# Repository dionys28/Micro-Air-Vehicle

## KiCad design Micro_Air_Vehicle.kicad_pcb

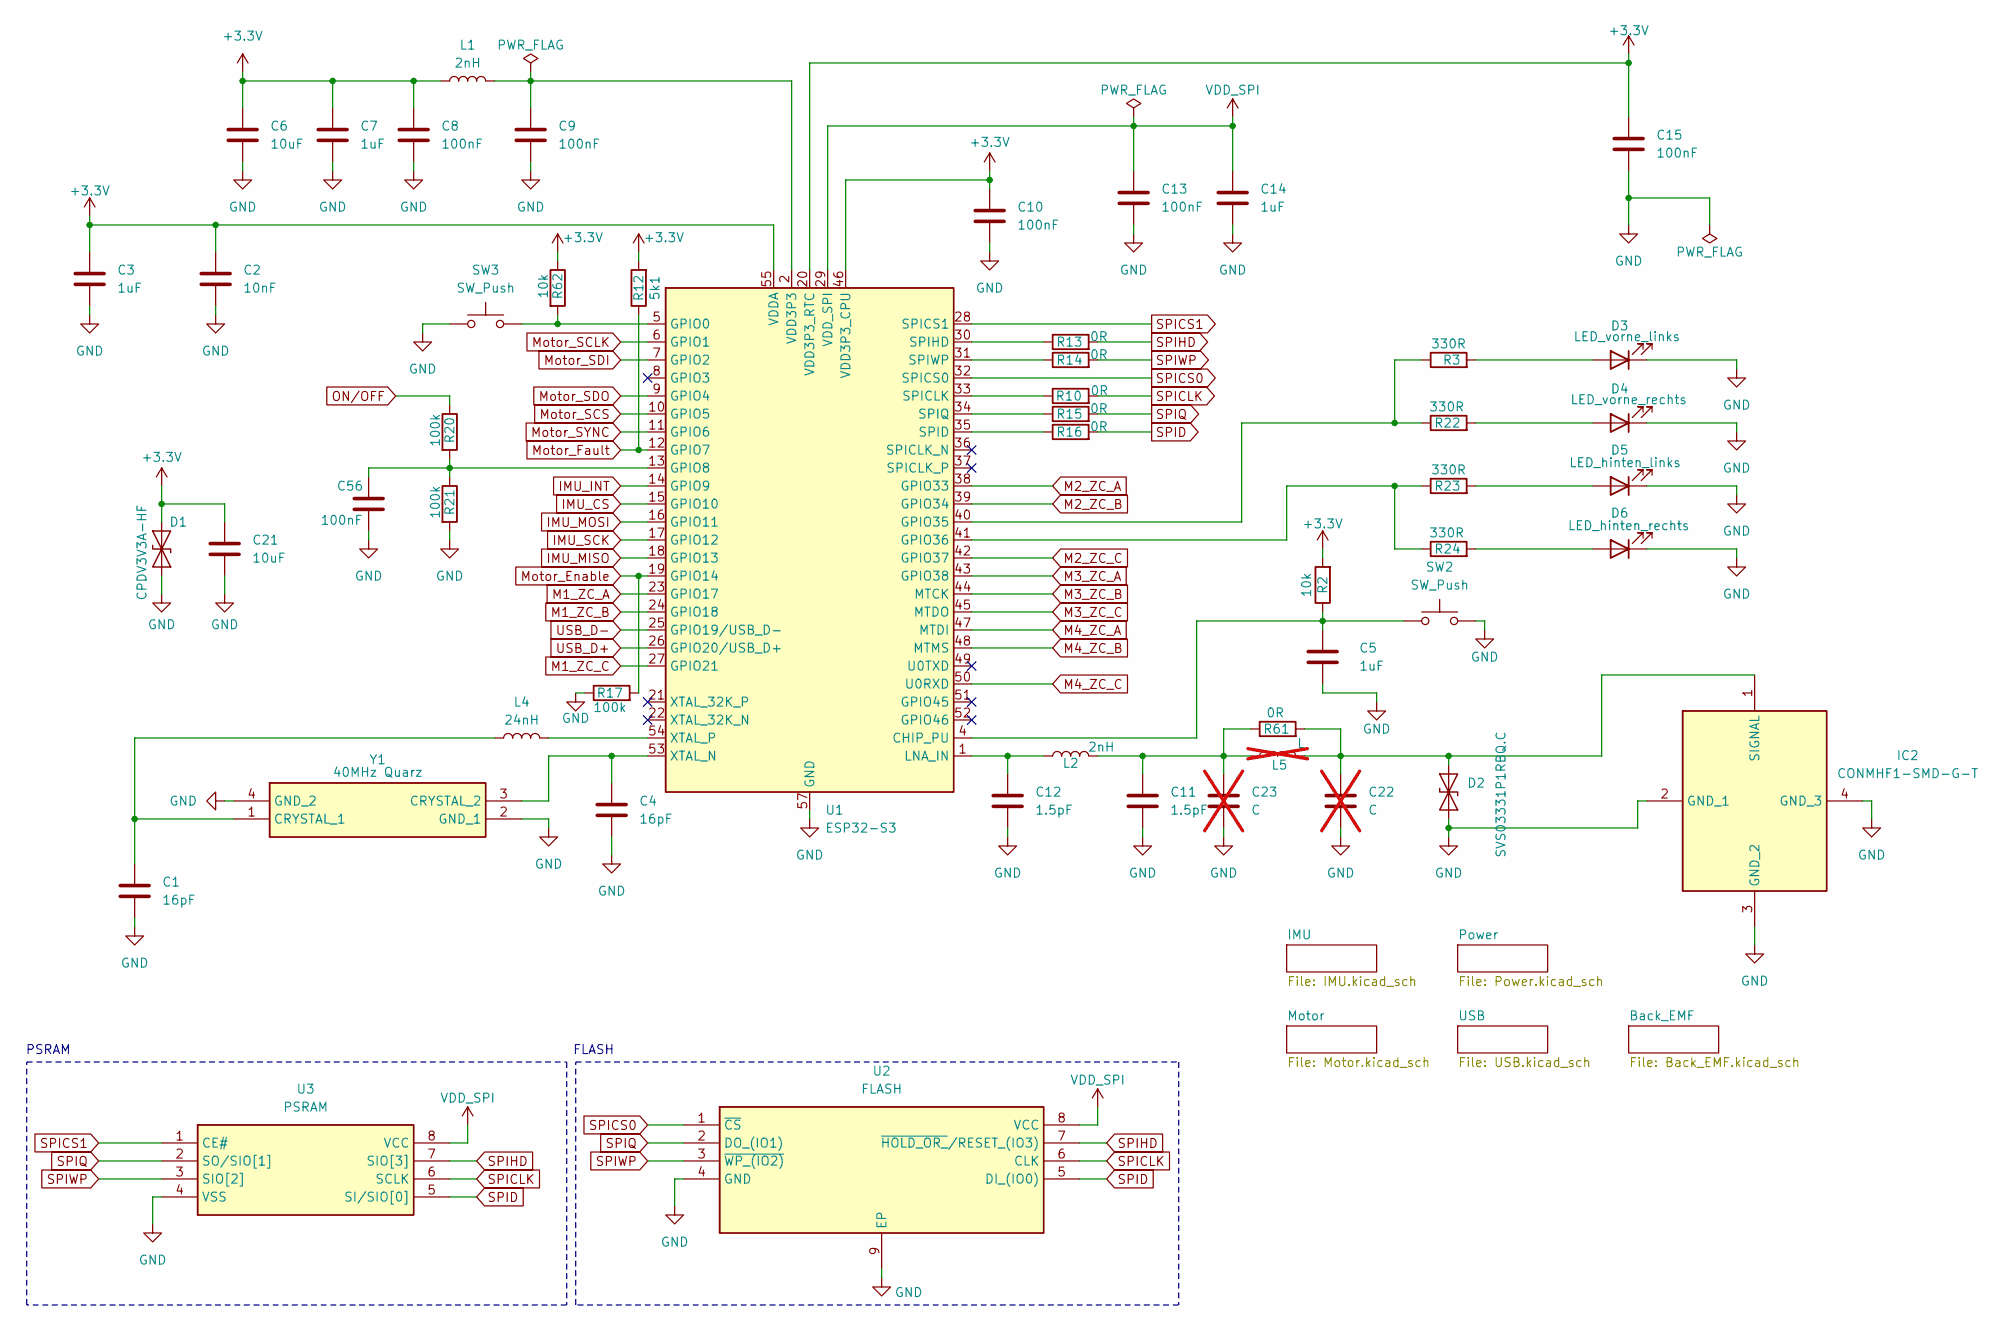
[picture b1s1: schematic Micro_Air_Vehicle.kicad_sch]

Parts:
C1, C4: 16pF; C_0603_1608Metric; LCSC Part # C1646
C2: 10nF; C_0603_1608Metric; LCSC Part # C1589
C3, C5, C7, C14: 1uF; C_0805_2012Metric; LCSC Part # C1712
C6, C21: 10uF; C_0805_2012Metric; LCSC Part # C15850
C8, C9, C10, C13, C15, C56: 100nF; C_0603_1608Metric; LCSC Part # C1590
C11, C12: 1.5pF; C_0201_0603Metric; LCSC Part # C50389
C22, C23: C; C_0201_0603Metric; not fitted
D1: CPDV3V3A-HF; Diode_D1; LCSC Part # C2594895
D2: SVS03331P1RBQ.C; LCSC Part # C19829538
D3: LED_vorne_links; LED_1206_3216Metric; LCSC Part # C219232
D4: LED_vorne_rechts; LED_1206_3216Metric; LCSC Part # C219232
D5: LED_hinten_links; LED_1206_3216Metric; LCSC Part # C49018
D6: LED_hinten_rechts; LED_1206_3216Metric; LCSC Part # C49018
IC2: CONMHF1-SMD-G-T; Antennen_Stecker; Mouser Part Number 712-CONMHF1-SMD-G-T
L1, L2: 2nH; L_0201_0603Metric; LCSC Part # C42142
L4: 24nH; L_0201_0603Metric; LCSC Part # C206441
L5: L; L_0201_0603Metric; not fitted
R2, R62: 10k; R_0603_1608Metric; LCSC Part # C15401
R3, R22, R23, R24: 330R; R_0603_1608Metric; LCSC Part # C22104
R10, R13, R14, R15, R16, R61: 0R; R_0603_1608Metric; LCSC Part # C21189
R12: 5k1; R_0603_1608Metric; LCSC Part # C14677
R17, R20, R21: 100k; R_0603_1608Metric; LCSC Part # C14675
SW2, SW3: SW_Push; SW_Push_1P1T_NO_CK_KMR2; LCSC Part # C99271
U1: ESP32-S3; QFN-56-1EP_7x7mm_P0.4mm_EP4x4mm; LCSC Part # C2913192
U2: FLASH; Mouser Part Number 454-W25Q64JVZPIM
U3: PSRAM; Mouser Part Number 485-4677
Y1: 40MHz Quarz; 40MHz_Quarz; Mouser Part Number 710-830108208709

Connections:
+3.3V: C2.1, C3.1, C6.1, C7.1, C8.1, C10.1, C15.1, C21.1, D1.2 (A2), L1.1, R2.2, R12.2, R62.1, U1.20 (VDD3P3_RTC), U1.46 (VDD3P3_CPU), U1.55 (VDDA), U1.56 (VDDA); also elsewhere on the board
GND: C1.2, C2.2, C3.2, C4.2, C5.2, C6.2, C7.2, C8.2, C9.2, C10.2, C11.2, C12.2, C13.2, C14.2, C15.2, C21.2, C22.2, C23.2, C56.2, D1.1 (A1), D2.1 (A1), D3.1 (K), D4.1 (K), D5.1 (K), D6.1 (K), IC2.2 (GND_1), IC2.3 (GND_2), IC2.4 (GND_3), R17.1, R21.2, SW2.2, SW3.1, U1.57 (GND), U2.4 (GND), U2.9 (EP), U3.4 (VSS), Y1.2 (GND_1), Y1.4 (GND_2); also elsewhere on the board
IMU_CS: U1.15 (GPIO10); also elsewhere on the board
IMU_INT: U1.14 (GPIO9); also elsewhere on the board
IMU_MISO: U1.18 (GPIO13); also elsewhere on the board
IMU_MOSI: U1.16 (GPIO11); also elsewhere on the board
IMU_SCK: U1.17 (GPIO12); also elsewhere on the board
M1_ZC_A: U1.23 (GPIO17); also elsewhere on the board
M1_ZC_B: U1.24 (GPIO18); also elsewhere on the board
M1_ZC_C: U1.27 (GPIO21); also elsewhere on the board
M2_ZC_A: U1.38 (GPIO33); also elsewhere on the board
M2_ZC_B: U1.39 (GPIO34); also elsewhere on the board
M2_ZC_C: U1.42 (GPIO37); also elsewhere on the board
M3_ZC_A: U1.43 (GPIO38); also elsewhere on the board
M3_ZC_B: U1.44 (MTCK); also elsewhere on the board
M3_ZC_C: U1.45 (MTDO); also elsewhere on the board
M4_ZC_A: U1.47 (MTDI); also elsewhere on the board
M4_ZC_B: U1.48 (MTMS); also elsewhere on the board
M4_ZC_C: U1.50 (U0RXD); also elsewhere on the board
Motor_Enable: R17.2, U1.19 (GPIO14); also elsewhere on the board
Motor_Fault: R12.1, U1.12 (GPIO7); also elsewhere on the board
Motor_SCLK: U1.6 (GPIO1); also elsewhere on the board
Motor_SCS: U1.10 (GPIO5); also elsewhere on the board
Motor_SDI: U1.7 (GPIO2); also elsewhere on the board
Motor_SDO: U1.9 (GPIO4); also elsewhere on the board
Motor_SYNC: U1.11 (GPIO6); also elsewhere on the board
unnamed: C9.1, L1.2, U1.2 (VDD3P3), U1.3 (VDD3P3)
unnamed: C11.1, C23.1, L2.2, L5.1, R61.1
unnamed: C22.1, D2.2 (A2), IC2.1 (SIGNAL), L5.2, R61.2
unnamed: D3.2 (A), R3.2
unnamed: D4.2 (A), R22.2
unnamed: D5.2 (A), R23.2
unnamed: D6.2 (A), R24.2
unnamed: C5.1, R2.1, SW2.1, U1.4 (CHIP_PU)
unnamed: R62.2, SW3.2, U1.5 (GPIO0)
unnamed: C56.1, R20.2, R21.1, U1.13 (GPIO8)
unnamed: R3.1, R22.1, U1.40 (GPIO35)
unnamed: R23.1, R24.1, U1.41 (GPIO36)
unnamed: C12.1, L2.1, U1.1 (LNA_IN)
unnamed: R10.1, U1.33 (SPICLK)
unnamed: R16.1, U1.35 (SPID)
unnamed: R13.1, U1.30 (SPIHD)
unnamed: R15.1, U1.34 (SPIQ)
unnamed: R14.1, U1.31 (SPIWP)
unnamed: C4.1, U1.53 (XTAL_N), Y1.3 (CRYSTAL_2)
unnamed: L4.2, U1.54 (XTAL_P)
unnamed: C1.1, L4.1, Y1.1 (CRYSTAL_1)
ON/OFF: R20.1; also elsewhere on the board
SPICLK: R10.2, U2.6 (CLK), U3.6 (SCLK)
SPICS0: U1.32 (SPICS0), U2.1 (~CS)
SPICS1: U1.28 (SPICS1), U3.1 (CE#)
SPID: R16.2, U2.5 (DI_(IO0)), U3.5 (SI/SIO[0])
SPIHD: R13.2, U2.7 (~HOLD_OR_/RESET_(IO3)), U3.7 (SIO[3])
SPIQ: R15.2, U2.2 (DO_(IO1)), U3.2 (SO/SIO[1])
SPIWP: R14.2, U2.3 (~WP_(IO2)), U3.3 (SIO[2])
USB_D+: U1.26 (GPIO20/USB_D+); also elsewhere on the board
USB_D-: U1.25 (GPIO19/USB_D-); also elsewhere on the board
VDD_SPI: C13.1, C14.1, U1.29 (VDD_SPI), U2.8 (VCC), U3.8 (VCC)

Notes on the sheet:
PSRAM
FLASH

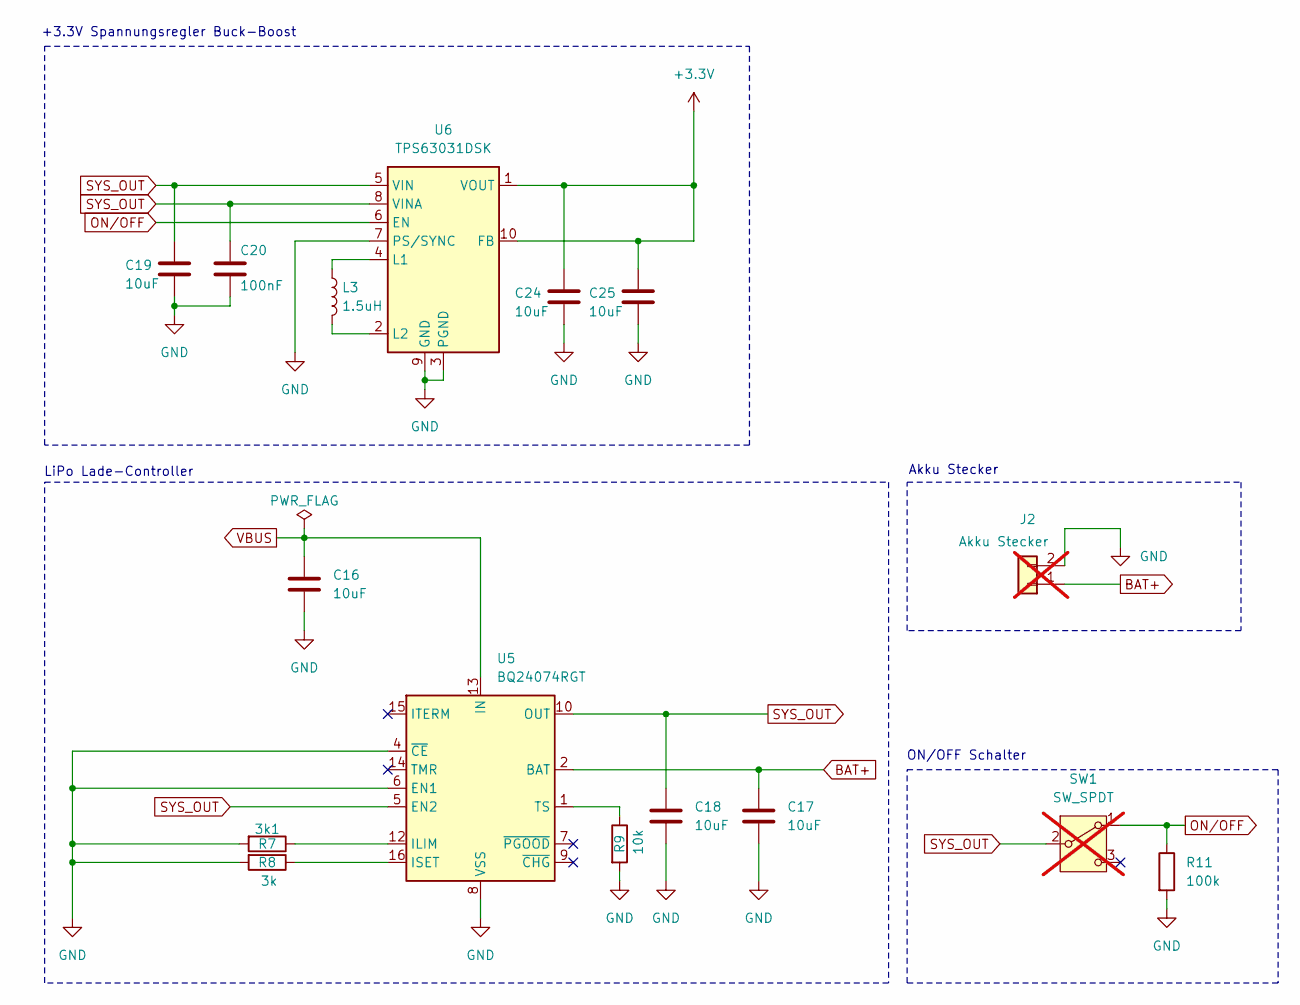
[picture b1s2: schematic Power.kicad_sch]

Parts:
C16, C17, C18, C19, C24, C25: 10uF; C_0805_2012Metric; LCSC Part # C15850
C20: 100nF; C_0603_1608Metric; LCSC Part # C1590
J2: Akku Stecker; SolderWire-1sqmm_1x02_P5.4mm_D1.4mm_OD2.7mm; not fitted
L3: 1.5uH; Spule1.5uH; LCSC Part # C2762016
R7: 3k1; R_0603_1608Metric; LCSC Part # C2924132
R8: 3k; R_0603_1608Metric; LCSC Part # C4211
R9: 10k; R_0603_1608Metric; LCSC Part # C15401
R11: 100k; R_0603_1608Metric; LCSC Part # C14675
SW1: SW_SPDT; SW_SPDT_CK_JS102011SAQN; not fitted
U5: BQ24074RGT; VQFN-16-1EP_3x3mm_P0.5mm_EP1.68x1.68mm_ThermalVias; LCSC Part # C54313
U6: TPS63031DSK; WSON-10-1EP_2.5x2.5mm_P0.5mm_EP1.2x2mm_ThermalVias; LCSC Part # C15516

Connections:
+3.3V: C24.1, C25.1, U6.1 (VOUT), U6.10 (FB); also elsewhere on the board
BAT+: C17.1, J2.1, U5.2 (BAT), U5.3 (BAT); also elsewhere on the board
GND: C16.2, C17.2, C18.2, C19.2, C20.2, C24.2, C25.2, J2.2, R7.2, R8.2, R9.2, R11.2, U5.4 (~CE), U5.6 (EN1), U5.8 (VSS), U5.17 (VSS), U6.3 (PGND), U6.7 (PS/SYNC), U6.9 (GND), U6.11 (PGND); also elsewhere on the board
unnamed: R7.1, U5.12 (ILIM)
unnamed: R8.1, U5.16 (ISET)
unnamed: R9.1, U5.1 (TS)
unnamed: L3.1, U6.4 (L1)
unnamed: L3.2, U6.2 (L2)
ON/OFF: R11.1, SW1.1 (A), U6.6 (EN); also elsewhere on the board
SYS_OUT: C18.1, C19.1, C20.1, SW1.2 (B), U5.5 (EN2), U5.10 (OUT), U5.11 (OUT), U6.5 (VIN), U6.8 (VINA); also elsewhere on the board
VBUS: C16.1, U5.13 (IN); also elsewhere on the board

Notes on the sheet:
ON/OFF Schalter
Akku Stecker
+3.3V Spannungsregler Buck-Boost
LiPo Lade-Controller

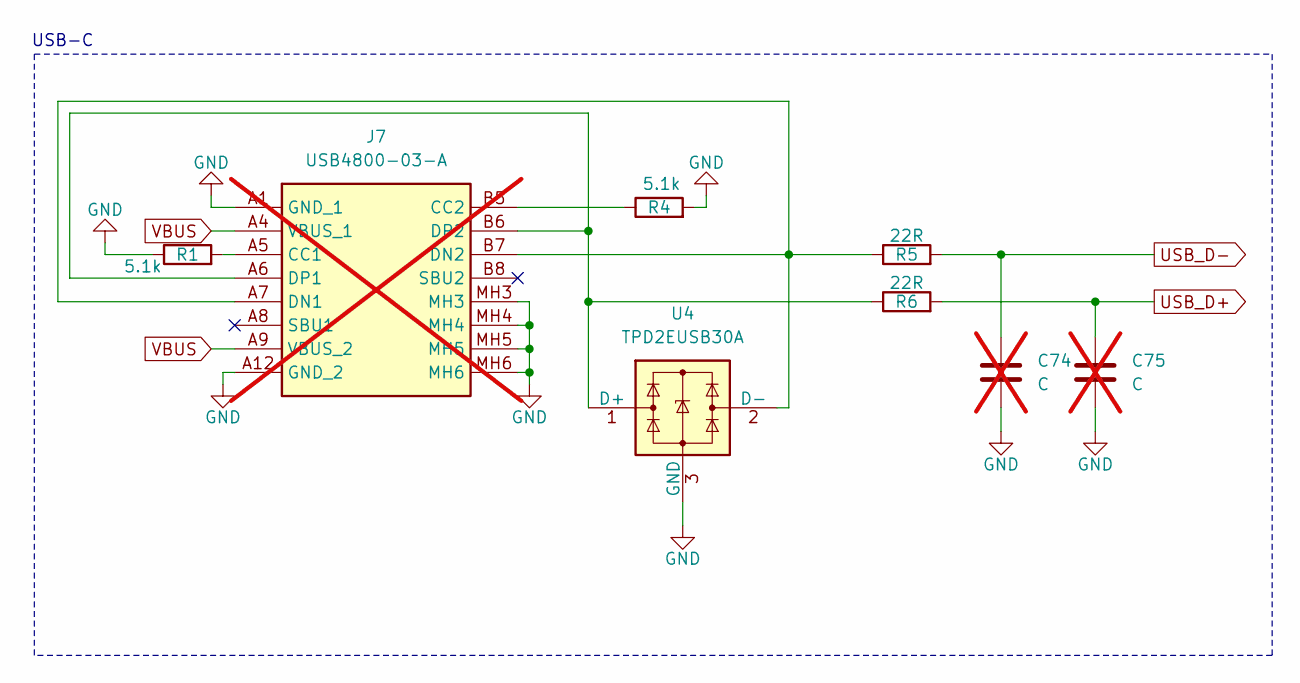
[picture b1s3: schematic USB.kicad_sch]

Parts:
C74, C75: C; C_0603_1608Metric; not fitted
J7: USB4800-03-A; USB480003A; Mouser Part Number 640-USB4800-03-A; not fitted
R1, R4: 5.1k; R_0603_1608Metric; LCSC Part # C14677
R5, R6: 22R; R_0603_1608Metric; LCSC Part # C1203
U4: TPD2EUSB30A; TPD2EUSB30ADRTR; LCSC Part # C94934

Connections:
GND: C74.2, C75.2, J7.A1 (GND_1), J7.A12 (GND_2), J7.MH3, J7.MH4, J7.MH5, J7.MH6, R1.1, R4.2, U4.3 (GND); also elsewhere on the board
unnamed: J7.A5 (CC1), R1.2
unnamed: J7.B5 (CC2), R4.1
unnamed: J7.A7 (DN1), J7.B7 (DN2), R5.1, U4.2 (D-)
unnamed: J7.A6 (DP1), J7.B6 (DP2), R6.1, U4.1 (D+)
USB_D+: C75.1, R6.2; also elsewhere on the board
USB_D-: C74.1, R5.2; also elsewhere on the board
VBUS: J7.A4 (VBUS_1), J7.A9 (VBUS_2); also elsewhere on the board

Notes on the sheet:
USB-C

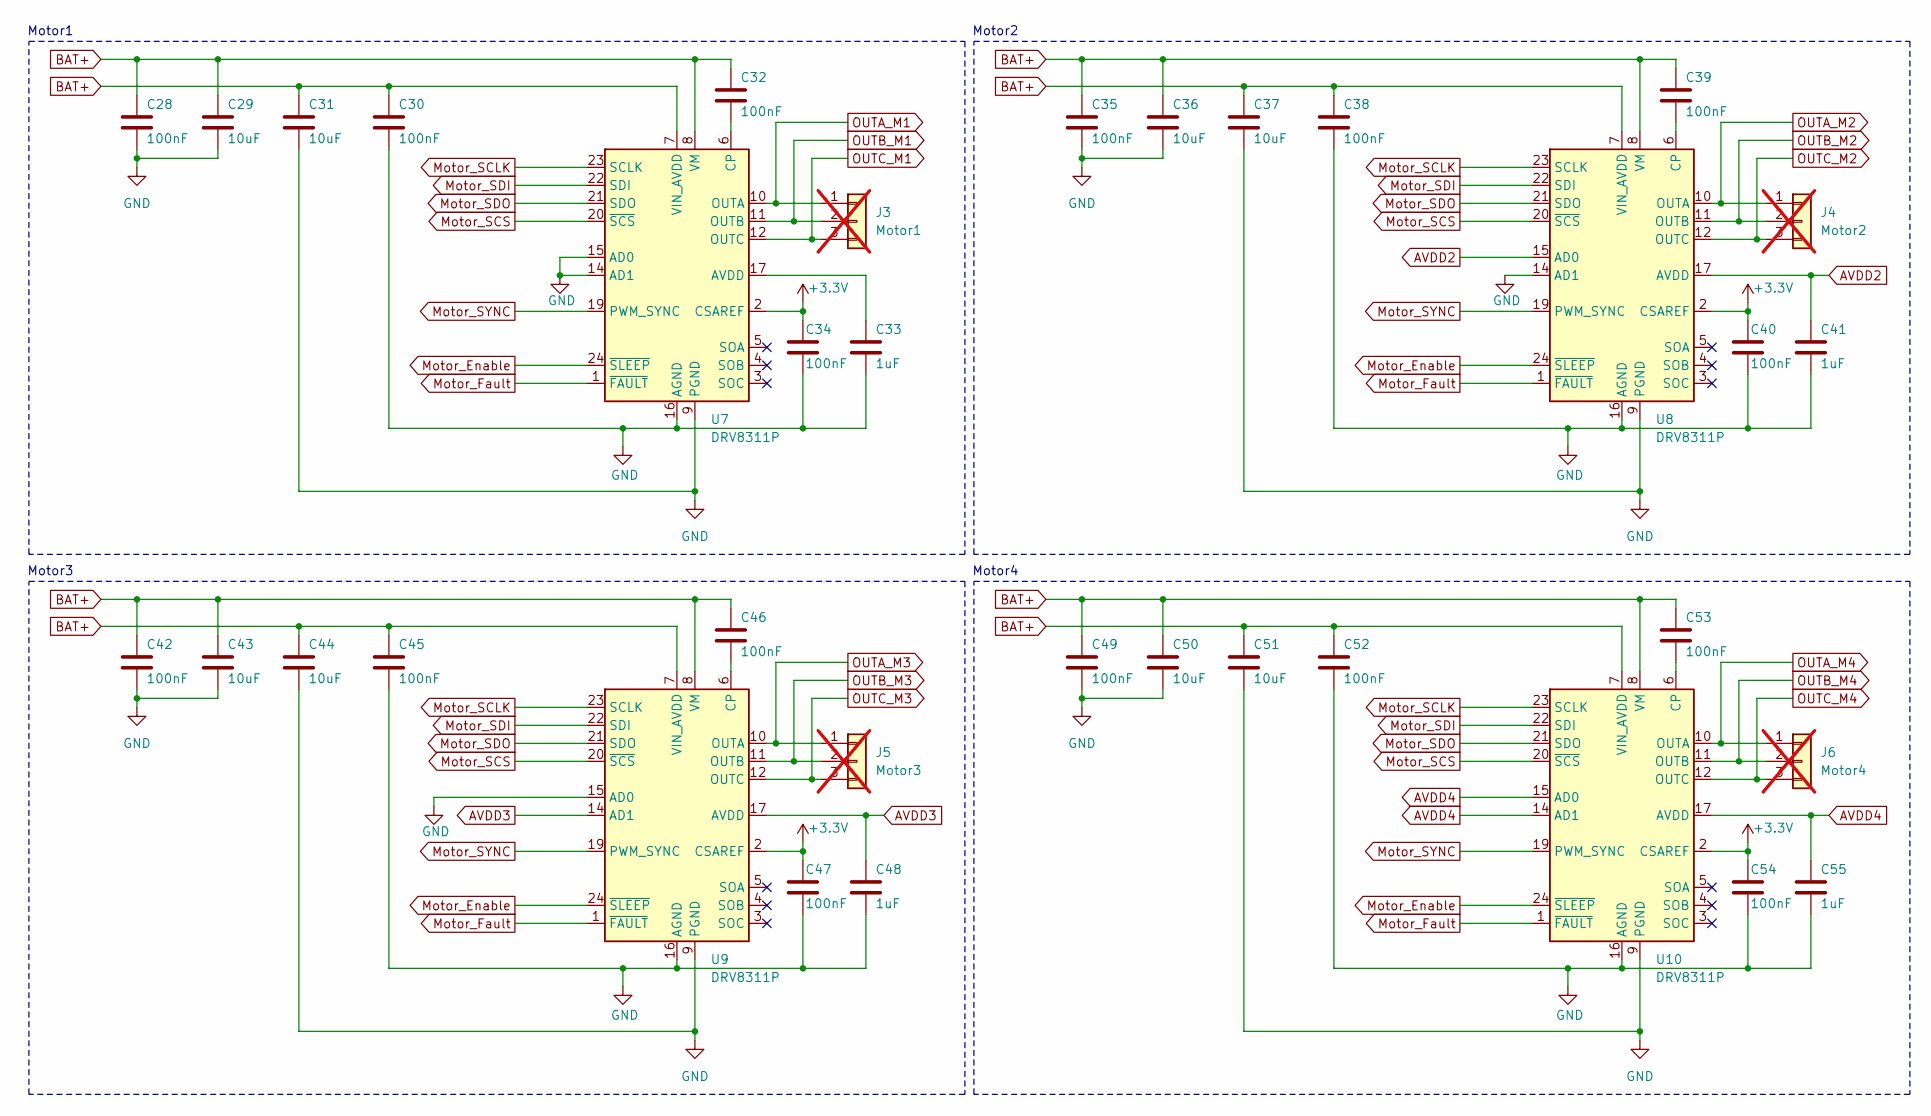
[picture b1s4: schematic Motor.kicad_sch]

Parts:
C28, C30, C32, C34, C35, C38, C39, C40, C42, C45, C46, C47, C49, C52, C53, C54: 100nF; C_0603_1608Metric; LCSC Part # C1590
C29, C31, C36, C37, C43, C44, C50, C51: 10uF; C_0805_2012Metric; LCSC Part # C15850
C33, C41, C48, C55: 1uF; C_0805_2012Metric; LCSC Part # C1712
J3: Motor1; SolderWire-0.1sqmm_1x03_P3.6mm_D0.4mm_OD1mm; not fitted
J4: Motor2; SolderWire-0.1sqmm_1x03_P3.6mm_D0.4mm_OD1mm; not fitted
J5: Motor3; SolderWire-0.1sqmm_1x03_P3.6mm_D0.4mm_OD1mm; not fitted
J6: Motor4; SolderWire-0.1sqmm_1x03_P3.6mm_D0.4mm_OD1mm; not fitted
U7, U8, U9, U10: DRV8311P; Texas_RRW0024A_WQFN-24-1EP_3x3mm_P0.4mm_EP1.9x1.9mm; LCSC Part # C3681458

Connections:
+3.3V: C34.1, C40.1, C47.1, C54.1, U7.2 (CSAREF), U8.2 (CSAREF), U9.2 (CSAREF), U10.2 (CSAREF); also elsewhere on the board
AVDD2: C41.1, U8.15 (AD0), U8.17 (AVDD)
AVDD3: C48.1, U9.14 (AD1), U9.17 (AVDD)
AVDD4: C55.1, U10.14 (AD1), U10.15 (AD0), U10.17 (AVDD)
BAT+: C28.1, C29.1, C30.1, C31.1, C32.1, C35.1, C36.1, C37.1, C38.1, C39.1, C42.1, C43.1, C44.1, C45.1, C46.1, C49.1, C50.1, C51.1, C52.1, C53.1, U7.7 (VIN_AVDD), U7.8 (VM), U8.7 (VIN_AVDD), U8.8 (VM), U9.7 (VIN_AVDD), U9.8 (VM), U10.7 (VIN_AVDD), U10.8 (VM); also elsewhere on the board
GND: C28.2, C29.2, C30.2, C31.2, C33.2, C34.2, C35.2, C36.2, C37.2, C38.2, C40.2, C41.2, C42.2, C43.2, C44.2, C45.2, C47.2, C48.2, C49.2, C50.2, C51.2, C52.2, C54.2, C55.2, U7.9 (PGND), U7.14 (AD1), U7.15 (AD0), U7.16 (AGND), U7.25 (PGND), U8.9 (PGND), U8.14 (AD1), U8.16 (AGND), U8.25 (PGND), U9.9 (PGND), U9.15 (AD0), U9.16 (AGND), U9.25 (PGND), U10.9 (PGND), U10.16 (AGND), U10.25 (PGND); also elsewhere on the board
Motor_Enable: U7.24 (~SLEEP), U8.24 (~SLEEP), U9.24 (~SLEEP), U10.24 (~SLEEP); also elsewhere on the board
Motor_Fault: U7.1 (~FAULT), U8.1 (~FAULT), U9.1 (~FAULT), U10.1 (~FAULT); also elsewhere on the board
Motor_SCLK: U7.23 (SCLK), U8.23 (SCLK), U9.23 (SCLK), U10.23 (SCLK); also elsewhere on the board
Motor_SCS: U7.20 (~SCS), U8.20 (~SCS), U9.20 (~SCS), U10.20 (~SCS); also elsewhere on the board
Motor_SDI: U7.22 (SDI), U8.22 (SDI), U9.22 (SDI), U10.22 (SDI); also elsewhere on the board
Motor_SDO: U7.21 (SDO), U8.21 (SDO), U9.21 (SDO), U10.21 (SDO); also elsewhere on the board
Motor_SYNC: U7.19 (PWM_SYNC), U8.19 (PWM_SYNC), U9.19 (PWM_SYNC), U10.19 (PWM_SYNC); also elsewhere on the board
unnamed: C33.1, U7.17 (AVDD)
unnamed: C32.2, U7.6 (CP)
unnamed: C39.2, U8.6 (CP)
unnamed: C46.2, U9.6 (CP)
unnamed: C53.2, U10.6 (CP)
OUTA_M1: J3.1, U7.10 (OUTA); also elsewhere on the board
OUTA_M2: J4.1, U8.10 (OUTA); also elsewhere on the board
OUTA_M3: J5.1, U9.10 (OUTA); also elsewhere on the board
OUTA_M4: J6.1, U10.10 (OUTA); also elsewhere on the board
OUTB_M1: J3.2, U7.11 (OUTB); also elsewhere on the board
OUTB_M2: J4.2, U8.11 (OUTB); also elsewhere on the board
OUTB_M3: J5.2, U9.11 (OUTB); also elsewhere on the board
OUTB_M4: J6.2, U10.11 (OUTB); also elsewhere on the board
OUTC_M1: J3.3, U7.12 (OUTC); also elsewhere on the board
OUTC_M2: J4.3, U8.12 (OUTC); also elsewhere on the board
OUTC_M3: J5.3, U9.12 (OUTC); also elsewhere on the board
OUTC_M4: J6.3, U10.12 (OUTC); also elsewhere on the board

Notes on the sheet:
Motor3
Motor2
Motor4
Motor1

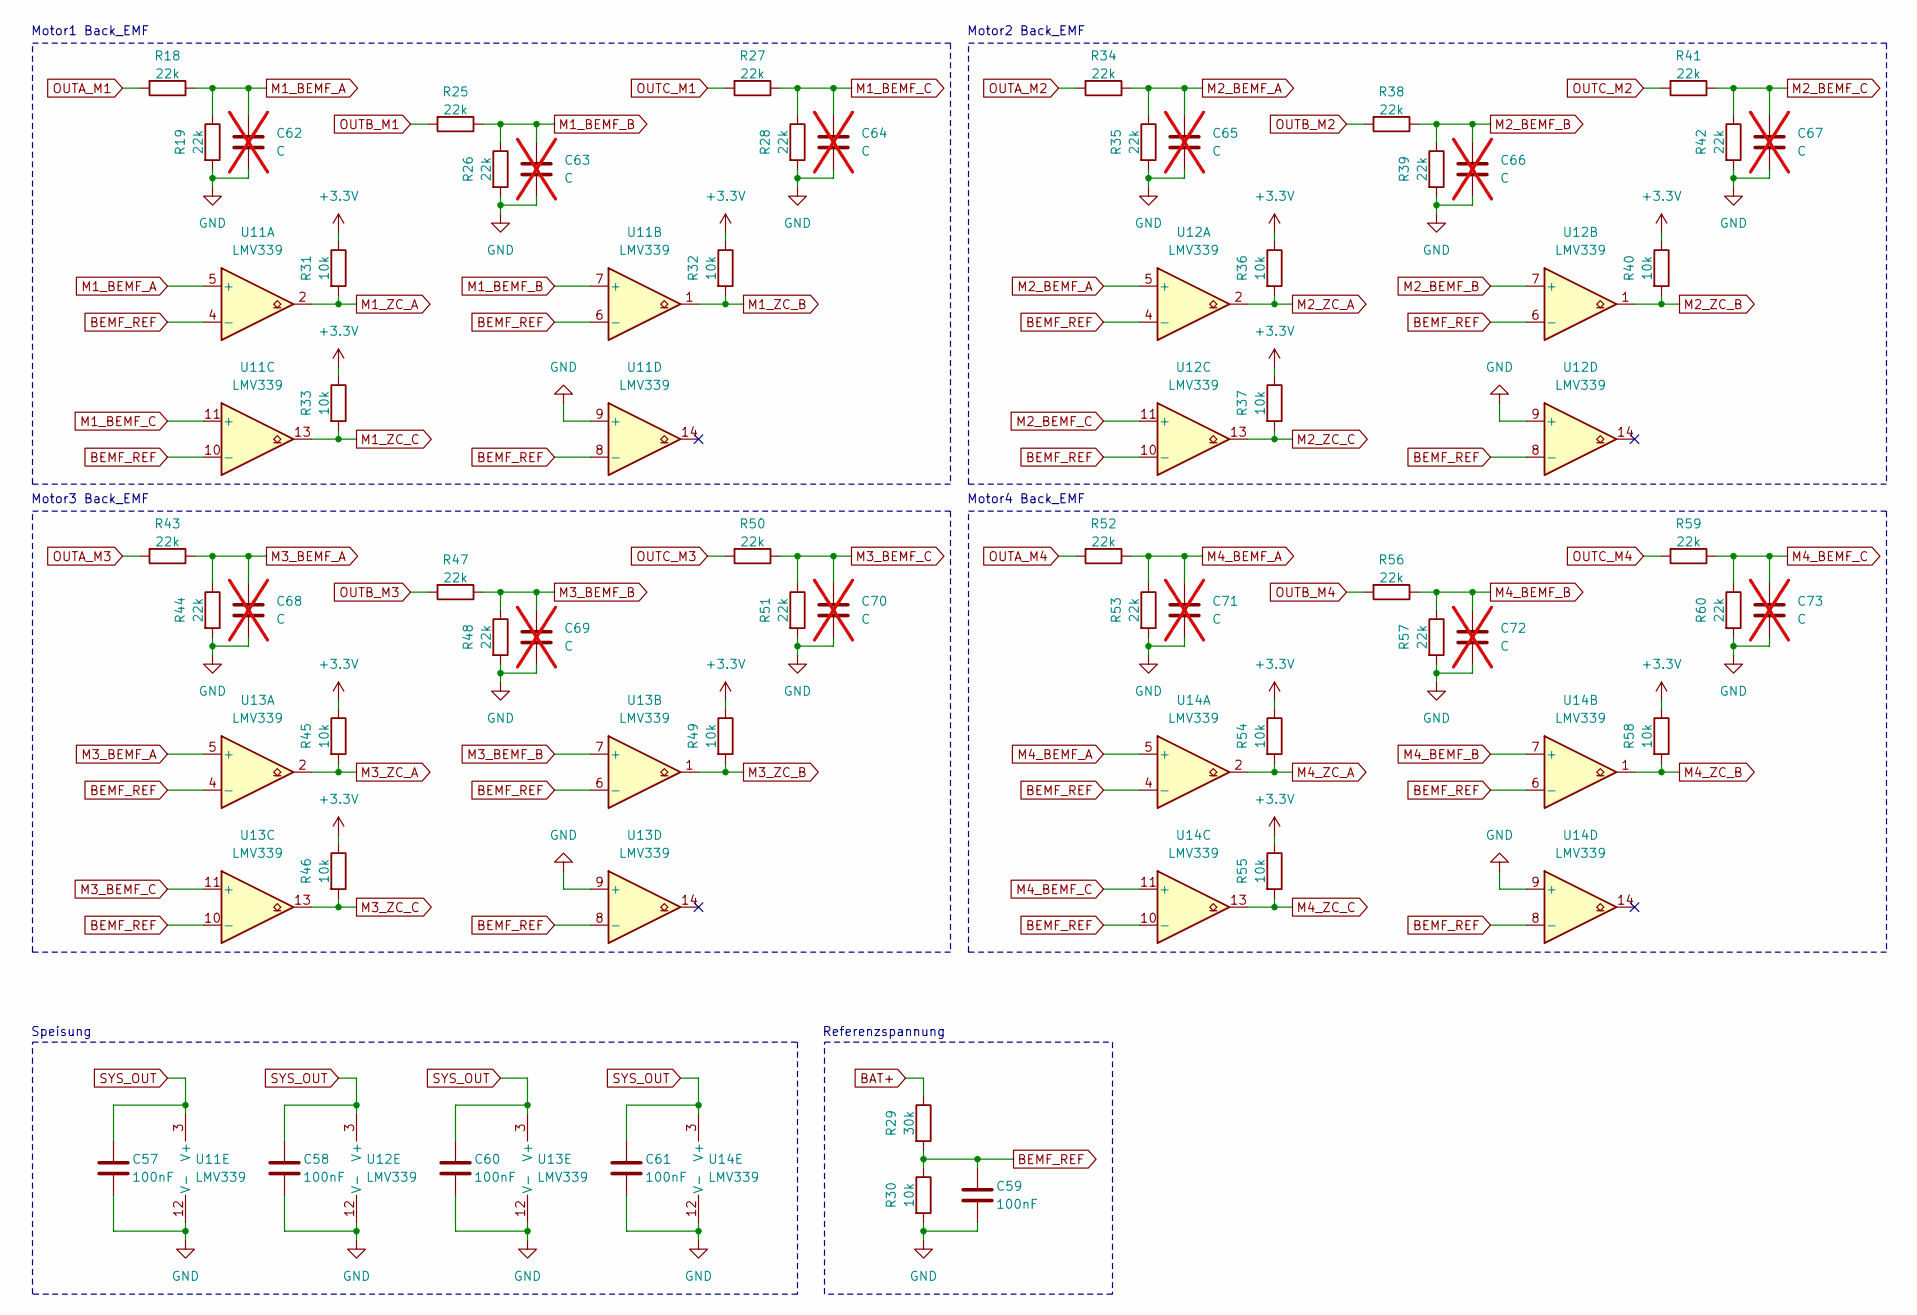
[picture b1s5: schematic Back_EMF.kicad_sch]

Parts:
C57, C58, C59, C60, C61: 100nF; C_0603_1608Metric; LCSC Part # C1590
C62, C63, C64, C65, C66, C67, C68, C69, C70, C71, C72, C73: C; C_0603_1608Metric; not fitted
R18, R19, R25, R26, R27, R28, R34, R35, R38, R39, R41, R42, R43, R44, R47, R48, R50, R51, R52, R53, R56, R57, R59, R60: 22k; R_0603_1608Metric; LCSC Part # C23344
R29: 30k; R_0603_1608Metric; LCSC Part # C18681
R30, R31, R32, R33, R36, R37, R40, R45, R46, R49, R54, R55, R58: 10k; R_0603_1608Metric; LCSC Part # C15401
U11, U12, U13, U14: LMV339; LMV339IPWR; LCSC Part # C273648

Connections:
+3.3V: R31.1, R32.1, R33.1, R36.1, R37.1, R40.1, R45.1, R46.1, R49.1, R54.1, R55.1, R58.1; also elsewhere on the board
BAT+: R29.1; also elsewhere on the board
BEMF_REF: C59.1, R29.2, R30.1, U11.4 (-), U11.6 (-), U11.8 (-), U11.10 (-), U12.4 (-), U12.6 (-), U12.8 (-), U12.10 (-), U13.4 (-), U13.6 (-), U13.8 (-), U13.10 (-), U14.4 (-), U14.6 (-), U14.8 (-), U14.10 (-)
GND: C57.2, C58.2, C59.2, C60.2, C61.2, C62.2, C63.2, C64.2, C65.2, C66.2, C67.2, C68.2, C69.2, C70.2, C71.2, C72.2, C73.2, R19.2, R26.2, R28.2, R30.2, R35.2, R39.2, R42.2, R44.2, R48.2, R51.2, R53.2, R57.2, R60.2, U11.9 (+), U11.12 (V-), U12.9 (+), U12.12 (V-), U13.9 (+), U13.12 (V-), U14.9 (+), U14.12 (V-); also elsewhere on the board
M1_BEMF_A: C62.1, R18.1, R19.1, U11.5 (+)
M1_BEMF_B: C63.1, R25.1, R26.1, U11.7 (+)
M1_BEMF_C: C64.1, R27.1, R28.1, U11.11 (+)
M1_ZC_A: R31.2, U11.2; also elsewhere on the board
M1_ZC_B: R32.2, U11.1; also elsewhere on the board
M1_ZC_C: R33.2, U11.13; also elsewhere on the board
M2_BEMF_A: C65.1, R34.1, R35.1, U12.5 (+)
M2_BEMF_B: C66.1, R38.1, R39.1, U12.7 (+)
M2_BEMF_C: C67.1, R41.1, R42.1, U12.11 (+)
M2_ZC_A: R36.2, U12.2; also elsewhere on the board
M2_ZC_B: R40.2, U12.1; also elsewhere on the board
M2_ZC_C: R37.2, U12.13; also elsewhere on the board
M3_BEMF_A: C68.1, R43.1, R44.1, U13.5 (+)
M3_BEMF_B: C69.1, R47.1, R48.1, U13.7 (+)
M3_BEMF_C: C70.1, R50.1, R51.1, U13.11 (+)
M3_ZC_A: R45.2, U13.2; also elsewhere on the board
M3_ZC_B: R49.2, U13.1; also elsewhere on the board
M3_ZC_C: R46.2, U13.13; also elsewhere on the board
M4_BEMF_A: C71.1, R52.1, R53.1, U14.5 (+)
M4_BEMF_B: C72.1, R56.1, R57.1, U14.7 (+)
M4_BEMF_C: C73.1, R59.1, R60.1, U14.11 (+)
M4_ZC_A: R54.2, U14.2; also elsewhere on the board
M4_ZC_B: R58.2, U14.1; also elsewhere on the board
M4_ZC_C: R55.2, U14.13; also elsewhere on the board
OUTA_M1: R18.2; also elsewhere on the board
OUTA_M2: R34.2; also elsewhere on the board
OUTA_M3: R43.2; also elsewhere on the board
OUTA_M4: R52.2; also elsewhere on the board
OUTB_M1: R25.2; also elsewhere on the board
OUTB_M2: R38.2; also elsewhere on the board
OUTB_M3: R47.2; also elsewhere on the board
OUTB_M4: R56.2; also elsewhere on the board
OUTC_M1: R27.2; also elsewhere on the board
OUTC_M2: R41.2; also elsewhere on the board
OUTC_M3: R50.2; also elsewhere on the board
OUTC_M4: R59.2; also elsewhere on the board
SYS_OUT: C57.1, C58.1, C60.1, C61.1, U11.3 (V+), U12.3 (V+), U13.3 (V+), U14.3 (V+); also elsewhere on the board

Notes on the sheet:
Motor3 Back_EMF
Motor2 Back_EMF
Motor4 Back_EMF
Referenzspannung
Motor1 Back_EMF
Speisung

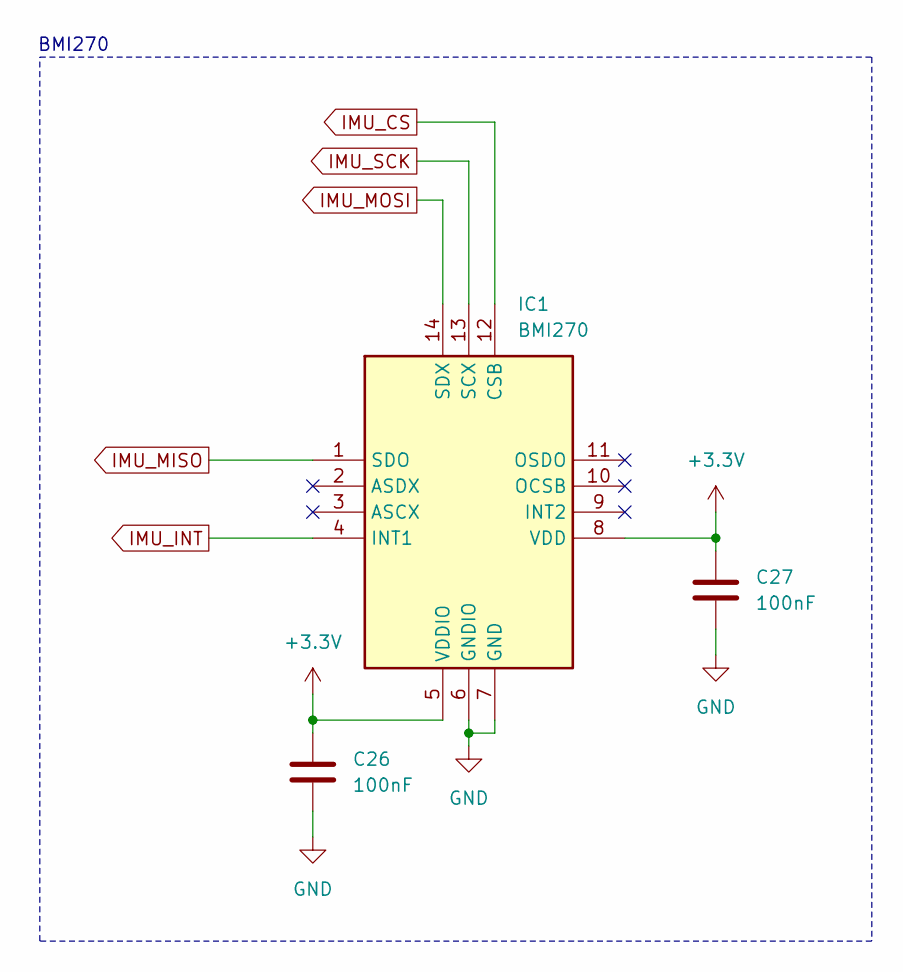
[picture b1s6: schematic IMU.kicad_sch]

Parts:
C26, C27: 100nF; C_0603_1608Metric; LCSC Part # C1590
IC1: BMI270; Mouser Part Number 262-BMI270

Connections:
+3.3V: C26.1, C27.1, IC1.5 (VDDIO), IC1.8 (VDD); also elsewhere on the board
GND: C26.2, C27.2, IC1.6 (GNDIO), IC1.7 (GND); also elsewhere on the board
IMU_CS: IC1.12 (CSB); also elsewhere on the board
IMU_INT: IC1.4 (INT1); also elsewhere on the board
IMU_MISO: IC1.1 (SDO); also elsewhere on the board
IMU_MOSI: IC1.14 (SDX); also elsewhere on the board
IMU_SCK: IC1.13 (SCX); also elsewhere on the board

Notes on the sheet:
BMI270
